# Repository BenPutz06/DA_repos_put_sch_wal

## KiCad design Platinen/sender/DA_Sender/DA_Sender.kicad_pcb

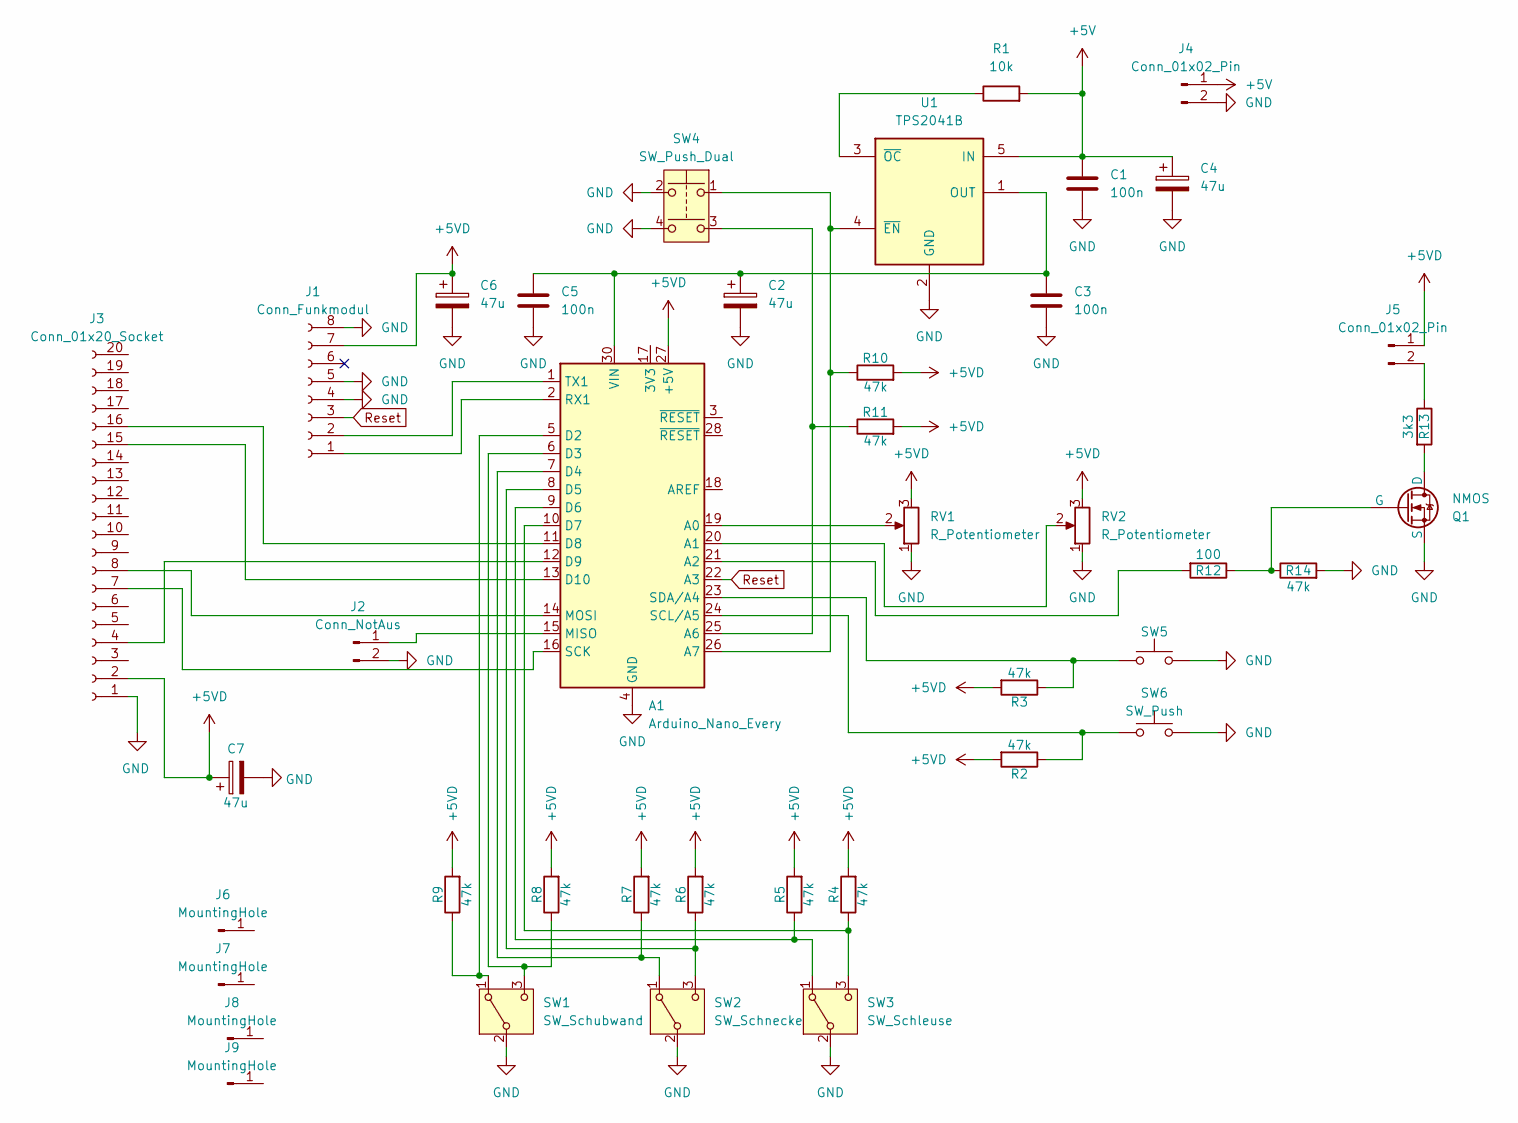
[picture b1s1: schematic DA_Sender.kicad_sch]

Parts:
A1: Arduino_Nano_Every; Arduino_Nano
C1, C3, C5: 100n; C_0805_2012Metric
C2, C4, C6, C7: 47u; CP_EIA-7343-30_AVX-N
J1: Conn_Funkmodul; PinHeader_1x08_P2.54mm_Horizontal
J2: Conn_NotAus; PinHeader_1x02_P2.54mm_Horizontal
J3: Conn_01x20_Socket; PinHeader_1x20_P2.54mm_Vertical
J4: Conn_01x02_Pin; PinHeader_1x02_P2.54mm_Horizontal
J5: Conn_01x02_Pin; PinHeader_1x02_P2.54mm_Vertical
J6, J7, J8, J9: MountingHole; MountingHole_2.7mm_M2.5
Q1: NMOS; TSOT-23; Part-NO FDV305N
R1: 10k; R_0805_2012Metric
R2, R3, R4, R5, R6, R7, R8, R9, R10, R11: 47k; R_0805_2012Metric
R12: 100; R_0805_2012Metric
R13: 3k3; R_0805_2012Metric; Part-NO CRG0603F3K3
R14: 47k; R_0805_2012Metric; Part-NO CRG0603F22K
RV1, RV2: R_Potentiometer; PinHeader_1x03_P2.54mm_Horizontal
SW1: SW_Schubwand; PinHeader_1x03_P2.54mm_Horizontal
SW2: SW_Schnecke; PinHeader_1x03_P2.54mm_Horizontal
SW3: SW_Schleuse; PinHeader_1x03_P2.54mm_Horizontal
SW4: SW_Push_Dual; PinHeader_1x03_P2.54mm_Horizontal
SW5, SW6: SW_Push; PinHeader_1x02_P2.54mm_Horizontal
U1: TPS2041B; SOIC-8_3.9x4.9mm_P1.27mm

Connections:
+5V: C1.1, C4.1, J4.1, R1.2, U1.5 (IN)
+5VD: A1.27 (+5V), C6.1, C7.1, J1.7, J3.2, J5.1, R2.2, R3.2, R4.2, R5.2, R6.2, R7.2, R8.2, R9.2, R10.2, R11.2, RV1.3, RV2.3
GND: A1.4 (GND), A1.29 (GND), C1.2, C2.2, C3.2, C4.2, C5.2, C6.2, C7.2, J1.4, J1.5, J1.8, J2.2, J3.1, J4.2, Q1.2 (S), R14.2, RV1.1, RV2.1, SW1.2 (B), SW2.2 (B), SW3.2 (B), SW4.2, SW4.4, SW5.2, SW6.2, U1.2 (GND)
unnamed: A1.19 (A0), RV1.2
unnamed: A1.20 (A1), RV2.2
unnamed: A1.21 (A2), R12.2
unnamed: A1.25 (A6), R11.1, SW4.3
unnamed: A1.26 (A7), R10.1, SW4.1, U1.4 (~EN)
unnamed: A1.5 (D2), R9.1, SW1.1 (A)
unnamed: A1.6 (D3), R8.1, SW1.3 (C)
unnamed: A1.7 (D4), R7.1, SW2.1 (A)
unnamed: A1.8 (D5), R6.1, SW2.3 (C)
unnamed: A1.9 (D6), R5.1, SW3.1 (A)
unnamed: A1.10 (D7), R4.1, SW3.3 (C)
unnamed: A1.11 (D8), J3.16
unnamed: A1.12 (D9), J3.4
unnamed: A1.13 (D10), J3.15
unnamed: A1.15 (MISO), J2.1
unnamed: A1.14 (MOSI), J3.8
unnamed: A1.2 (RX1), J1.1
unnamed: A1.16 (SCK), J3.7
unnamed: A1.24 (SCL/A5), R2.1, SW6.1
unnamed: A1.23 (SDA/A4), R3.1, SW5.1
unnamed: A1.1 (TX1), J1.2
unnamed: A1.30 (VIN), C2.1, C3.1, C5.1, U1.1 (OUT)
unnamed: J5.2, R13.1
unnamed: Q1.3 (D), R13.2
unnamed: Q1.1 (G), R12.1, R14.1
unnamed: R1.1, U1.3 (~OC)
Reset: A1.22 (A3), J1.3

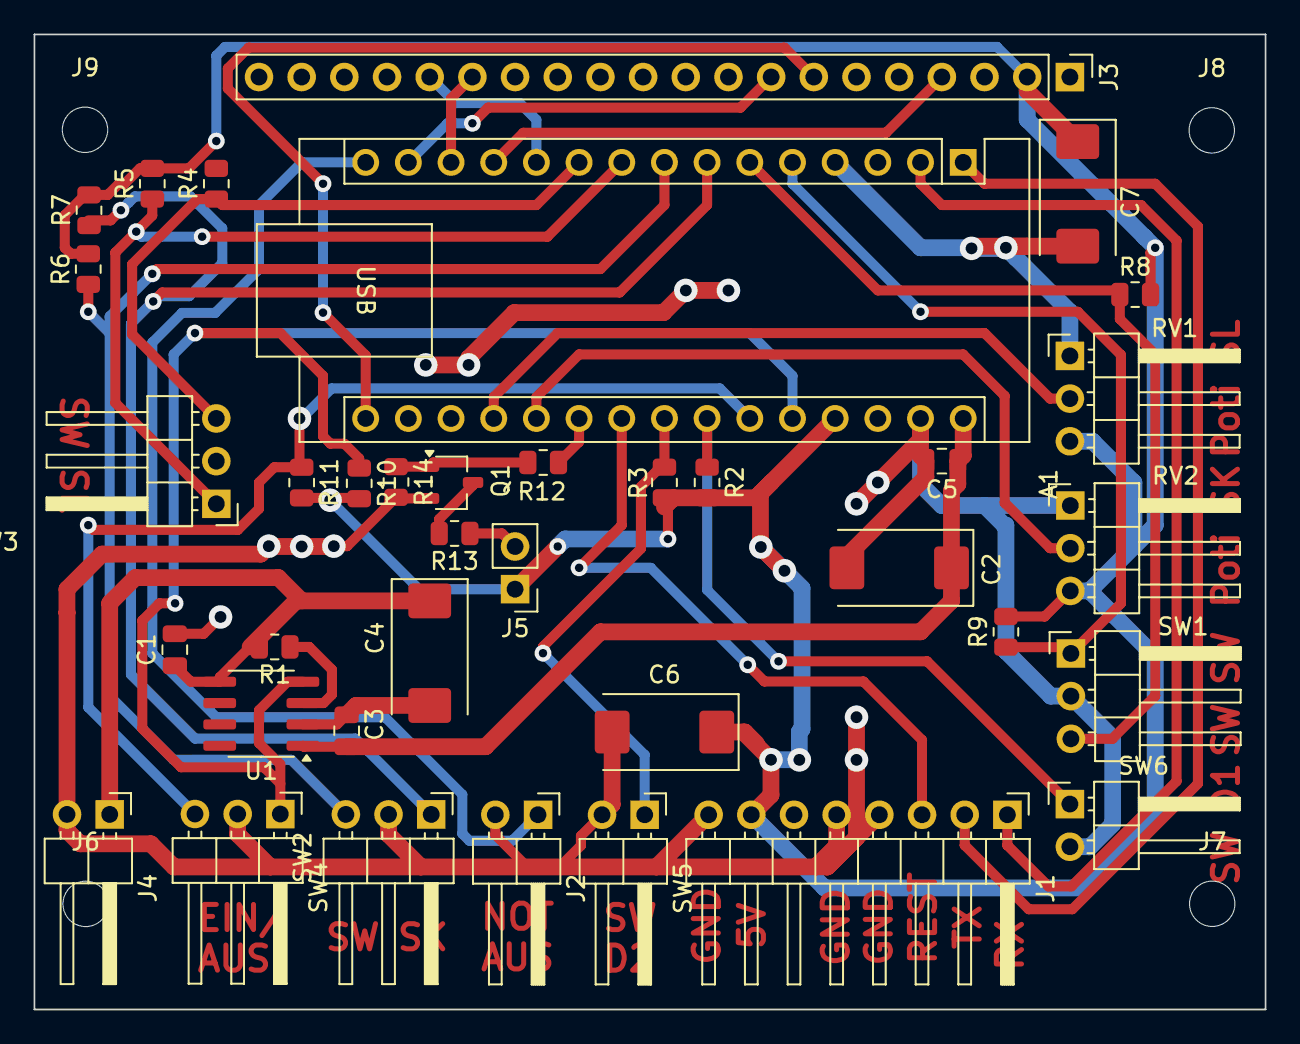
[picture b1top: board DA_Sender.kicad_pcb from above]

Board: 2 copper layers, 73.3 x 58.0 mm, 41 parts (0 on the bottom side), 30 nets.

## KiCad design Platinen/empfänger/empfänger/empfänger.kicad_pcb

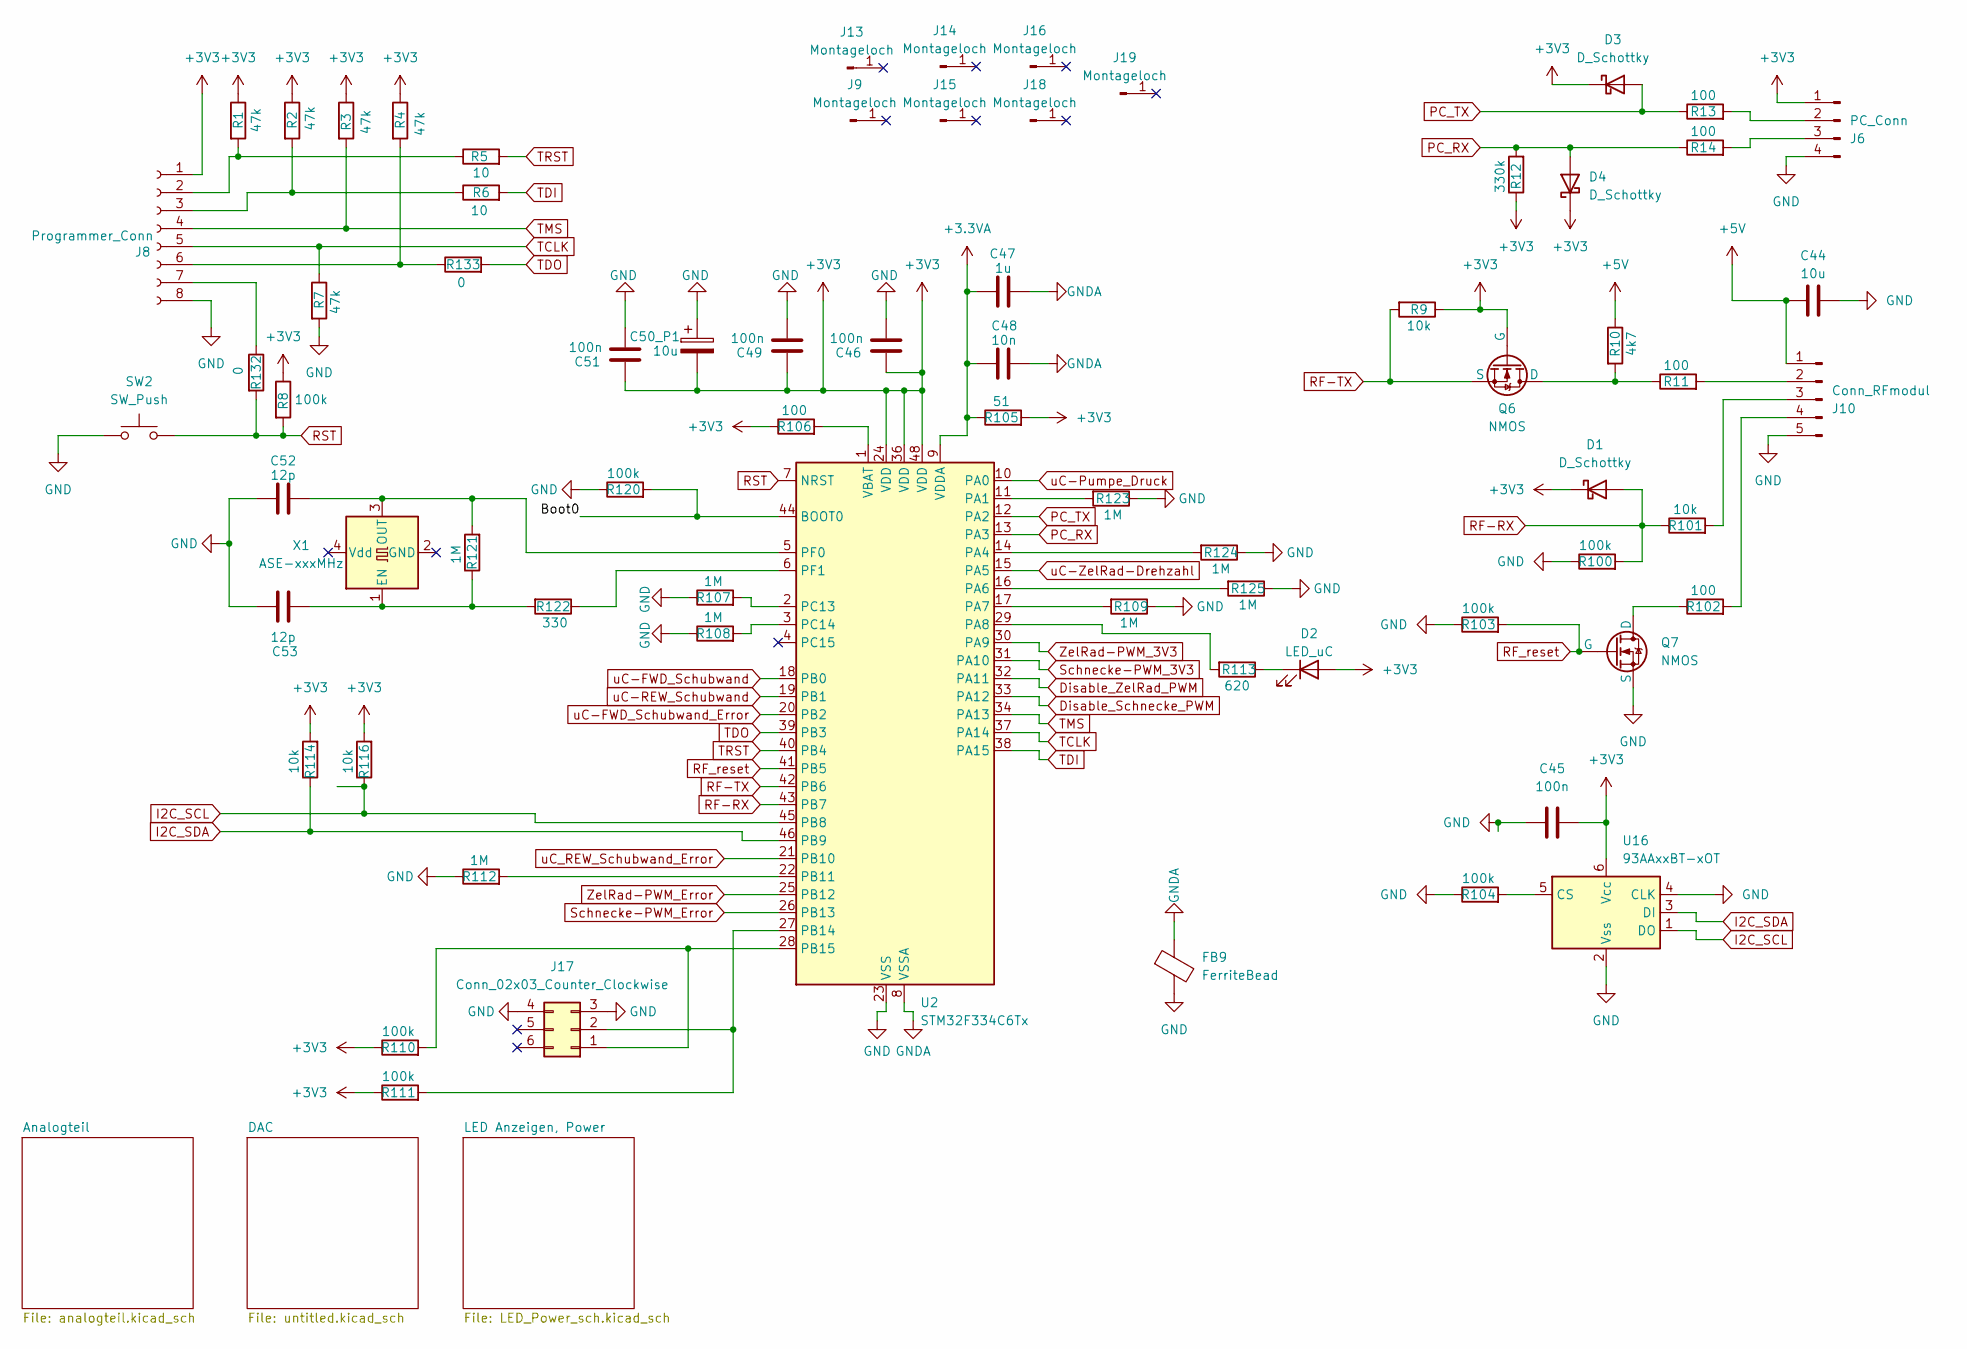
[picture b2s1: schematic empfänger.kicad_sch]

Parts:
C44: 10u; C_1206_3216Metric; Part-NO C1206C106K4RAC
C45, C46, C49, C51: 100n; C_0805_2012Metric; Part-NO CC0805KRX7R9BB104
C47: 1u; C_1206_3216Metric; Part-NO C1206C105K4RAC
C48: 10n; C_0603_1608Metric; Part-NO CC0603KRX7R9BB103
C50_P1: 10u; C_1206_3216Metric; Part-NO B45196H2106K109
C52, C53: 12p; C_0603_1608Metric; Part-NO CC0603JRNPO9BN120
D1, D3, D4: D_Schottky; D_SOD-123; Part-NO MBR0530_30V_0A5
D2: LED_uC; LED_0603_1608Metric; Part-NO SML_512MW
FB9: FerriteBead; R_1206_3216Metric; Part-NO WE-CBF_74279218
J6: PC_Conn; TerminalBlock_Phoenix_PTSM-0,5-4-2.5-V-THR_1x04_P2.50mm_Ver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; Part-NO MCV-0_5-4-G-2_5
J8: Programmer_Conn; Molex_PicoBlade_53047-0810_1x08_P1.25mm_Vertical; Part-NO 53047-0810
J9, J13, J14, J15, J16, J18, J19: Montageloch; MountingHole_5mm
J10: Conn_RFmodul; TeminalBlock_Phoenix_5Pol; Part-NO MCV-0_5-5-G-2_5
J17: Conn_02x03_Counter_Clockwise; PinHeader_2x03_P2.54mm_Vertical; Part-NO TSW-102-07-T-T
Q6, Q7: NMOS; TSOT-23; Part-NO FDV305N
R1, R2, R3, R4, R7: 47k; R_0603_1608Metric; Part-NO CRG0603F47K
R5, R6: 10; R_0603_1608Metric
R8, R100, R103, R104, R110, R111, R120: 100k; R_0603_1608Metric; Part-NO CRG0603F100K
R9, R101, R114, R116: 10k; R_0603_1608Metric; Part-NO CRG0603F10K
R10: 4k7; R_0603_1608Metric; Part-NO CRG0603F4K7
R11, R102, R106: 100; R_0603_1608Metric
R12: 330k; R_0603_1608Metric; Part-NO CRG0603F100R
R13, R14: 100; R_1206_3216Metric
R105: 51; R_1206_3216Metric; Part-NO CRG1206F51R
R107, R108, R109, R112, R121, R123, R124, R125: 1M; R_0603_1608Metric; Part-NO CRG0603F1M0
R113: 620; R_0603_1608Metric; Part-NO CRG0603F620R
R122: 330; R_0603_1608Metric; Part-NO CRG0603F330R
R132, R133: 0; R_0603_1608Metric; Part-NO CRG0603ZR
SW2: SW_Push; SW_Push_1P1T_NO_6x6mm_H9.5mm; Part-NO PHAP3368
U2: STM32F334C6Tx; LQFP-48_7x7mm_P0.5mm; Part-NO STM32F334C6T6TRDKR
U16: 93AAxxBT-xOT; SOT-23-6; Part-NO 24AA025E48
X1: ASE-xxxMHz; Crystal_SMD_5032-4Pin_5.0x3.2mm; Part-NO Q_8_JXG53P4-12-30/50-LF-T1

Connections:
+3.3VA: C47.2, C48.2, R105.1, U2.9 (VDDA); also elsewhere on the board
+3V3: C45.2, C46.2, C49.2, C50_P1.2, C51.2, D1.1 (K), D2.2 (A), D3.1 (K), D4.1 (K), J6.1, J8.1, Q6.1 (G), R1.1, R2.1, R3.1, R4.1, R8.1, R9.1, R12.1, R105.2, R106.1, R110.1, R111.1, R114.2, R116.2, U2.24 (VDD), U2.36 (VDD), U2.48 (VDD), U16.6 (Vcc); also elsewhere on the board
+5V: C44.1, J10.1, R10.1
/Boot0: R120.2, U2.44 (BOOT0)
Disable_Schnecke_PWM: U2.33 (PA12); also elsewhere on the board
Disable_ZelRad_PWM: U2.32 (PA11); also elsewhere on the board
GND: C44.2, C45.1, C46.1, C49.1, C50_P1.1, C51.1, C52.2, C53.1, FB9.2, J6.4, J8.8, J10.5, J17.3, J17.4, Q7.2 (S), R7.2, R100.1, R103.1, R104.1, R107.1, R108.1, R109.1, R112.1, R120.1, R123.1, R124.1, R125.1, SW2.1, U2.23 (VSS), U2.35 (VSS), U2.47 (VSS), U16.2 (Vss), U16.4 (CLK); also elsewhere on the board
GNDA: C47.1, C48.1, FB9.1, U2.8 (VSSA); also elsewhere on the board
I2C_SCL: R116.1, U2.45 (PB8), U16.1 (DO)
I2C_SDA: R114.1, U2.46 (PB9), U16.3 (DI)
unnamed: D2.1 (K), R113.1
unnamed: J6.2, R13.2
unnamed: J6.3, R14.2
unnamed: J8.2, R1.2, R5.1
unnamed: J8.3, R2.2, R6.1
unnamed: J8.6, R4.2, R133.1
unnamed: J8.7, R132.1
unnamed: J10.2, R11.2
unnamed: J10.3, R101.2
unnamed: J10.4, R102.2
unnamed: J17.1, R110.2, U2.28 (PB15)
unnamed: J17.2, R111.2, U2.27 (PB14)
unnamed: Q6.3 (D), R10.2, R11.1
unnamed: Q7.3 (D), R102.1
unnamed: R123.2, U2.11 (PA1)
unnamed: R124.2, U2.14 (PA4)
unnamed: R125.2, U2.16 (PA6)
unnamed: R109.2, U2.17 (PA7)
unnamed: R113.2, U2.29 (PA8)
unnamed: R112.2, U2.22 (PB11)
unnamed: R107.2, U2.2 (PC13)
unnamed: R108.2, U2.3 (PC14)
unnamed: C52.1, R121.2, U2.5 (PF0), X1.3 (OUT)
unnamed: R122.1, U2.6 (PF1)
unnamed: R106.2, U2.1 (VBAT)
unnamed: R104.2, U16.5 (CS)
unnamed: C53.2, R121.1, R122.2, X1.1 (EN)
PC_RX: D4.2 (A), R12.2, R14.1, U2.13 (PA3)
PC_TX: D3.2 (A), R13.1, U2.12 (PA2)
RF-RX: D1.2 (A), R100.2, R101.1, U2.43 (PB7)
RF-TX: Q6.2 (S), R9.2, U2.42 (PB6)
RF_reset: Q7.1 (G), R103.2, U2.41 (PB5)
RST: R8.2, R132.2, SW2.2, U2.7 (NRST)
Schnecke-PWM_3V3: U2.31 (PA10); also elsewhere on the board
Schnecke-PWM_Error: U2.26 (PB13); also elsewhere on the board
TCLK: J8.5, R7.1, U2.37 (PA14)
TDI: R6.2, U2.38 (PA15)
TDO: R133.2, U2.39 (PB3)
TMS: J8.4, R3.2, U2.34 (PA13)
TRST: R5.2, U2.40 (PB4)
ZelRad-PWM_3V3: U2.30 (PA9); also elsewhere on the board
ZelRad-PWM_Error: U2.25 (PB12); also elsewhere on the board
uC-FWD_Schubwand: U2.18 (PB0); also elsewhere on the board
uC-FWD_Schubwand_Error: U2.20 (PB2); also elsewhere on the board
uC-Pumpe_Druck: U2.10 (PA0); also elsewhere on the board
uC-REW_Schubwand: U2.19 (PB1); also elsewhere on the board
uC-ZelRad-Drehzahl: U2.15 (PA5); also elsewhere on the board
uC_REW_Schubwand_Error: U2.21 (PB10); also elsewhere on the board

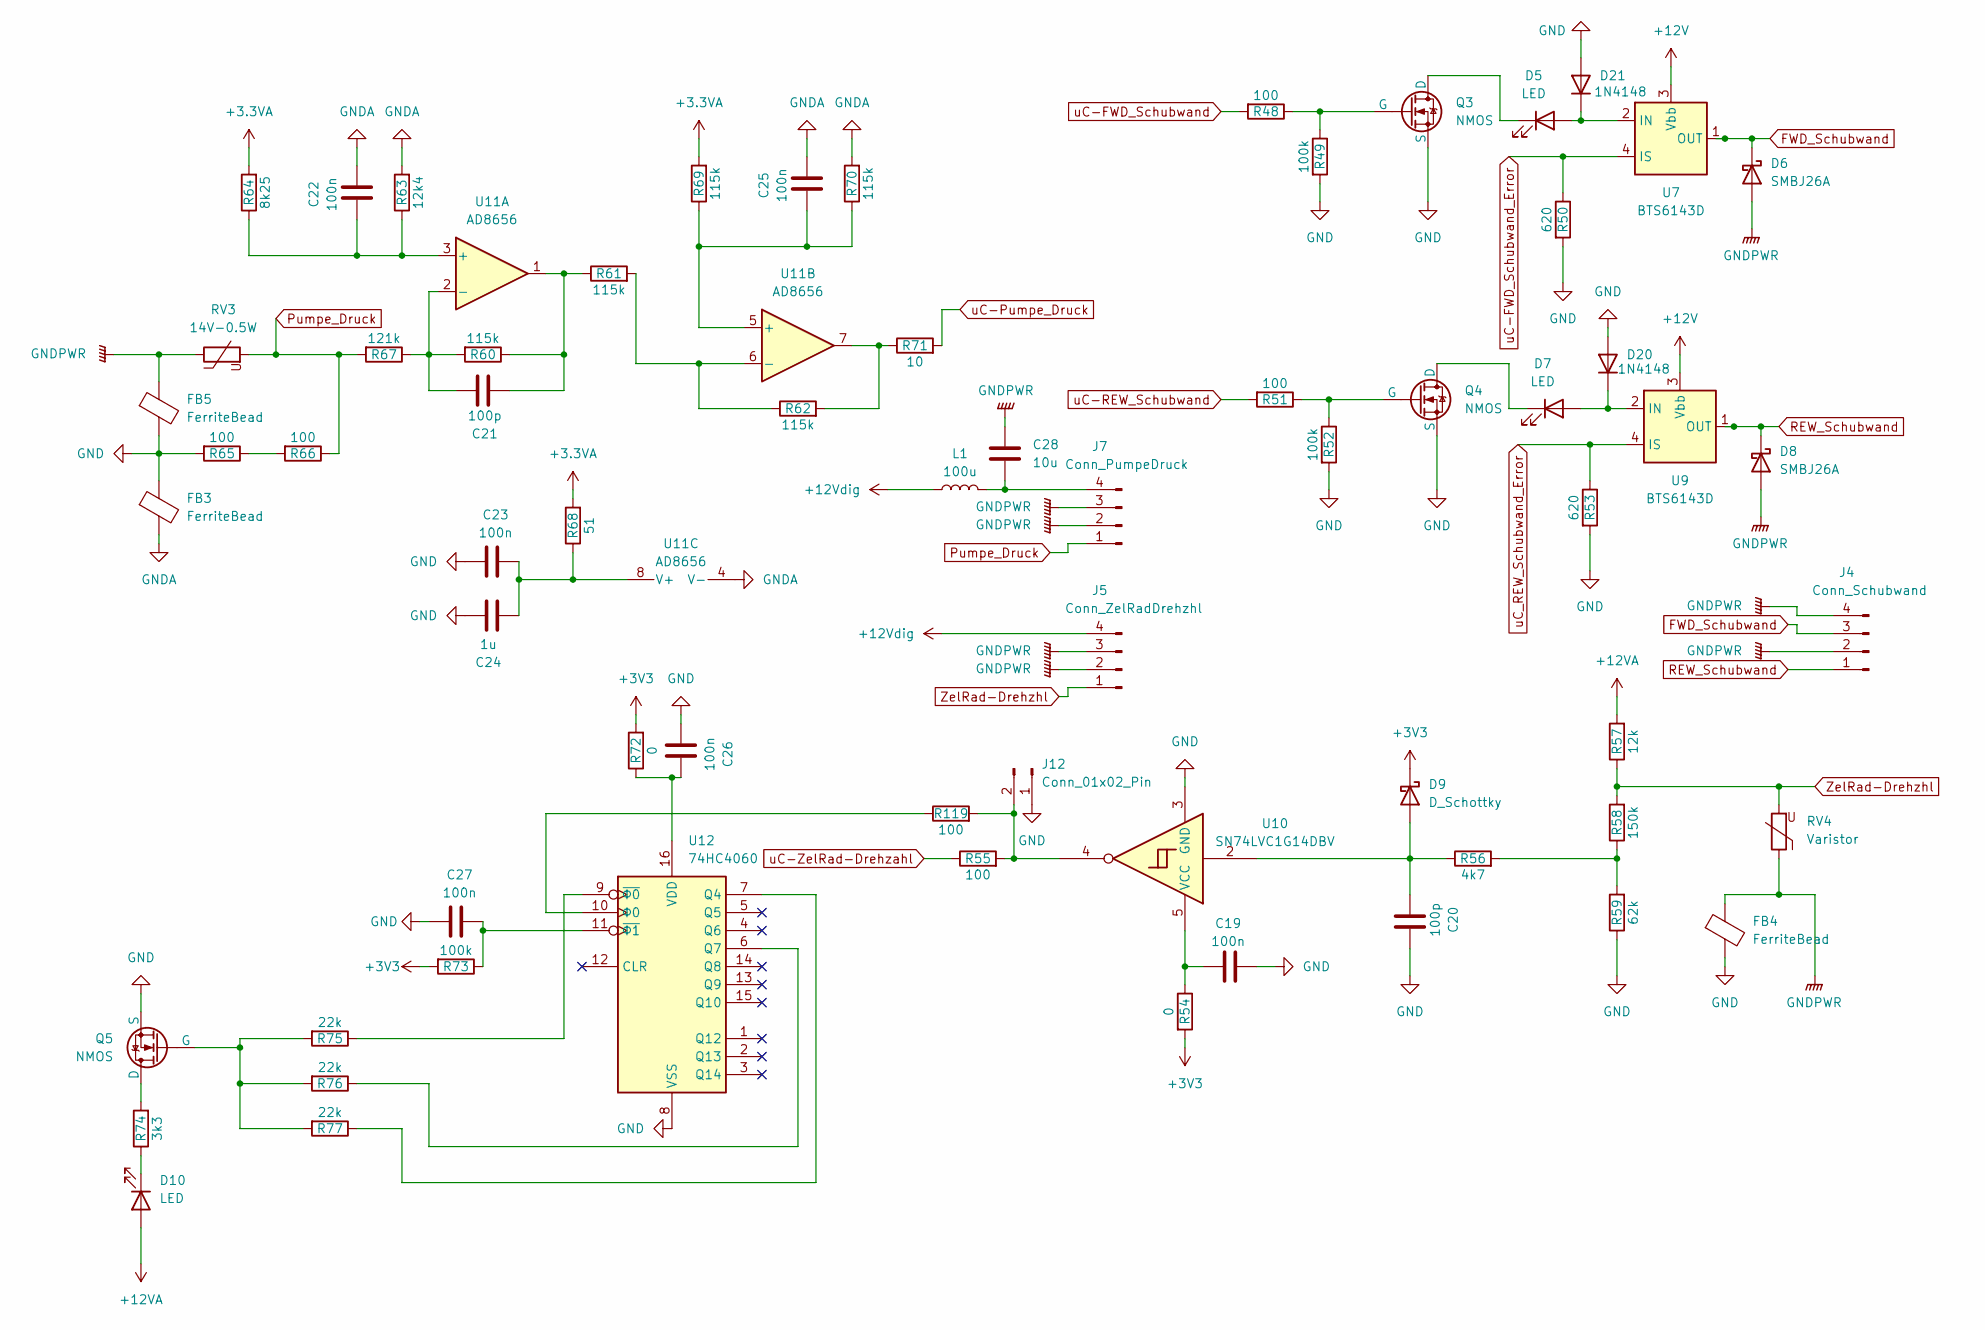
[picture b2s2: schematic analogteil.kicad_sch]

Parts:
C19, C22, C25, C26, C27: 100n; C_0805_2012Metric; Part-NO CC0805KRX7R9BB104
C20, C21: 100p; C_0805_2012Metric; Part-NO C0805C101J5GACTU
C23: 100n; C_0805_2012Metric; Part-NO CC0603KRX7R9BB103
C24: 1u; C_1206_3216Metric; Part-NO C1206C105K4RAC
C28: 10u; C_1206_3216Metric; Part-NO C1206C106K4RAC
D5, D7, D10: LED; LED_0805_2012Metric; Part-NO XZCDGK54W-1VF
D6, D8: SMBJ26A; D_SMB; Part-NO SMBJ26A
D9: D_Schottky; D_SOD-123; Part-NO MBR0530_30V_0A5
D20, D21: 1N4148; D_DO-35_SOD27_P2.54mm_Vertical_AnodeUp; Part-NO 1N4148WS_ES_08
FB3, FB4, FB5: FerriteBead; R_1206_3216Metric; Part-NO WE-CBF_74279218
J4: Conn_Schubwand; PhoenixContact_MSTBVA_2,5_4-G-5,08_1x04_P5.08mm_Vertical; Part-NO MSTBV2_5/4-G-5_08
J5: Conn_ZelRadDrehzhl; PhoenixContact_MSTBVA_2,5_4-G-5,08_1x04_P5.08mm_Vertical; Part-NO MSTBV2_5/4-G-5_08
J7: Conn_PumpeDruck; PhoenixContact_MSTBVA_2,5_4-G-5,08_1x04_P5.08mm_Vertical; Part-NO MSTBV2_5/4-G-5_08
J12: Conn_01x02_Pin; PinHeader_1x02_P2.54mm_Vertical; Part-NO JMP_1X2P_0901200122
L1: 100u; L_Sunlord_SWPA6045S; Part-NO 74404064101
Q3, Q4, Q5: NMOS; TSOT-23; Part-NO FDV305N
R48, R51, R55, R119: 100; R_0603_1608Metric
R49, R52, R73: 100k; R_0603_1608Metric; Part-NO CRG0603F100K
R50, R53: 620; R_0603_1608Metric; Part-NO CRG0603F620R
R54, R72: 0; R_0603_1608Metric; Part-NO CRG0603ZR
R56: 4k7; R_0603_1608Metric; Part-NO CRG0603F4K7
R57: 12k; R_1206_3216Metric; Part-NO CRG1206F12K
R58: 150k; R_0603_1608Metric; Part-NO CRG0603F150K
R59: 62k; R_0603_1608Metric; Part-NO CRG0603F62K
R60, R61, R62, R69, R70: 115k; R_0805_2012Metric; Part-NO RR1220Q-1153-D-M
R63: 12k4; R_0805_2012Metric; Part-NO RR1220Q-1242-D-M
R64: 8k25; R_0805_2012Metric; Part-NO RR1220Q-8251-D-M
R65, R66: 100; R_0805_2012Metric
R67: 121k; R_0805_2012Metric; Part-NO RR1220Q-1213-D-M
R68: 51; R_1206_3216Metric; Part-NO CRG1206F51R
R71: 10; R_0603_1608Metric
R74: 3k3; R_0603_1608Metric; Part-NO CRG0603F3K3
R75, R76, R77: 22k; R_0603_1608Metric; Part-NO CRG0603F22K
RV3: 14V-0.5W; R_1206_3216Metric; Part-NO WE-VS_82541110
RV4: Varistor; R_1206_3216Metric; Part-NO WE-VS_82541110
U7, U9: BTS6143D; TO-252-4; Part-NO BTS6143DAUMA1
U10: SN74LVC1G14DBV; SOT-23-5; Part-NO SN74LVC1G14DBVR
U11: AD8656; SOIC-8_3.9x4.9mm_P1.27mm; Part-NO AD8656ARZ
U12: 74HC4060; SOIC-16_3.9x9.9mm_P1.27mm; Part-NO SN74HC4040D

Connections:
+3.3VA: R64.2, R68.2, R69.2; also elsewhere on the board
+3V3: D9.1 (K), R54.2, R72.2, R73.2; also elsewhere on the board
+12V: U7.3 (Vbb), U9.3 (Vbb); also elsewhere on the board
+12VA: D10.2 (A), R57.2; also elsewhere on the board
+12Vdig: J5.4, L1.1; also elsewhere on the board
FWD_Schubwand: D6.1 (K), J4.3, U7.1 (OUT), U7.5 (OUT)
GND: C19.2, C20.2, C23.1, C24.2, C26.1, C27.1, D20.2 (A), D21.2 (A), FB3.1, FB4.2, FB5.2, J12.1, Q3.2 (S), Q4.2 (S), Q5.2 (S), R49.2, R50.2, R52.2, R53.2, R59.1, R65.2, U10.3 (GND), U12.8 (VSS); also elsewhere on the board
GNDA: C22.2, C25.2, FB3.2, R63.2, R70.2, U11.4 (V-); also elsewhere on the board
GNDPWR: C28.1, D6.2 (A), D8.2 (A), FB4.1, FB5.1, J4.2, J4.4, J5.2, J5.3, J7.2, J7.3, RV3.1, RV4.1; also elsewhere on the board
unnamed: C21.1, R60.1, R61.1, U11.1
unnamed: D5.1 (K), Q3.3 (D)
unnamed: D7.1 (K), Q4.3 (D)
unnamed: C20.1, D9.2 (A), R56.1, U10.2
unnamed: D10.1 (K), R74.1
unnamed: D7.2 (A), D20.1 (K), U9.2 (IN)
unnamed: D5.2 (A), D21.1 (K), U7.2 (IN)
unnamed: C28.2, J7.4, L1.2
unnamed: J12.2, R55.2, R119.2, U10.4
unnamed: Q3.1 (G), R48.1, R49.1
unnamed: Q4.1 (G), R51.1, R52.1
unnamed: Q5.3 (D), R74.2
unnamed: Q5.1 (G), R75.2, R76.2, R77.2
unnamed: R56.2, R58.1, R59.2
unnamed: R62.2, R71.1, U11.7
unnamed: R65.1, R66.2
unnamed: C19.1, R54.1, U10.5 (VCC)
unnamed: C22.1, R63.1, R64.1, U11.3 (+)
unnamed: C21.2, R60.2, R67.1, U11.2 (-)
unnamed: C25.1, R69.1, R70.1, U11.5 (+)
unnamed: R61.2, R62.1, U11.6 (-)
unnamed: C23.2, C24.1, R68.1, U11.8 (V+)
unnamed: R77.1, U12.7 (Q4)
unnamed: R76.1, U12.6 (Q7)
unnamed: C26.2, R72.1, U12.16 (VDD)
unnamed: R75.1, U12.9 (~Φ0)
unnamed: C27.2, R73.1, U12.11 (~Φ1)
unnamed: R119.1, U12.10 (Φ0)
Pumpe_Druck: J7.1, R66.1, R67.2, RV3.2
REW_Schubwand: D8.1 (K), J4.1, U9.1 (OUT), U9.5 (OUT)
ZelRad-Drehzhl: J5.1, R57.1, R58.2, RV4.2
uC-FWD_Schubwand: R48.2; also elsewhere on the board
uC-FWD_Schubwand_Error: R50.1, U7.4 (IS); also elsewhere on the board
uC-Pumpe_Druck: R71.2; also elsewhere on the board
uC-REW_Schubwand: R51.2; also elsewhere on the board
uC-ZelRad-Drehzahl: R55.1; also elsewhere on the board
uC_REW_Schubwand_Error: R53.1, U9.4 (IS); also elsewhere on the board

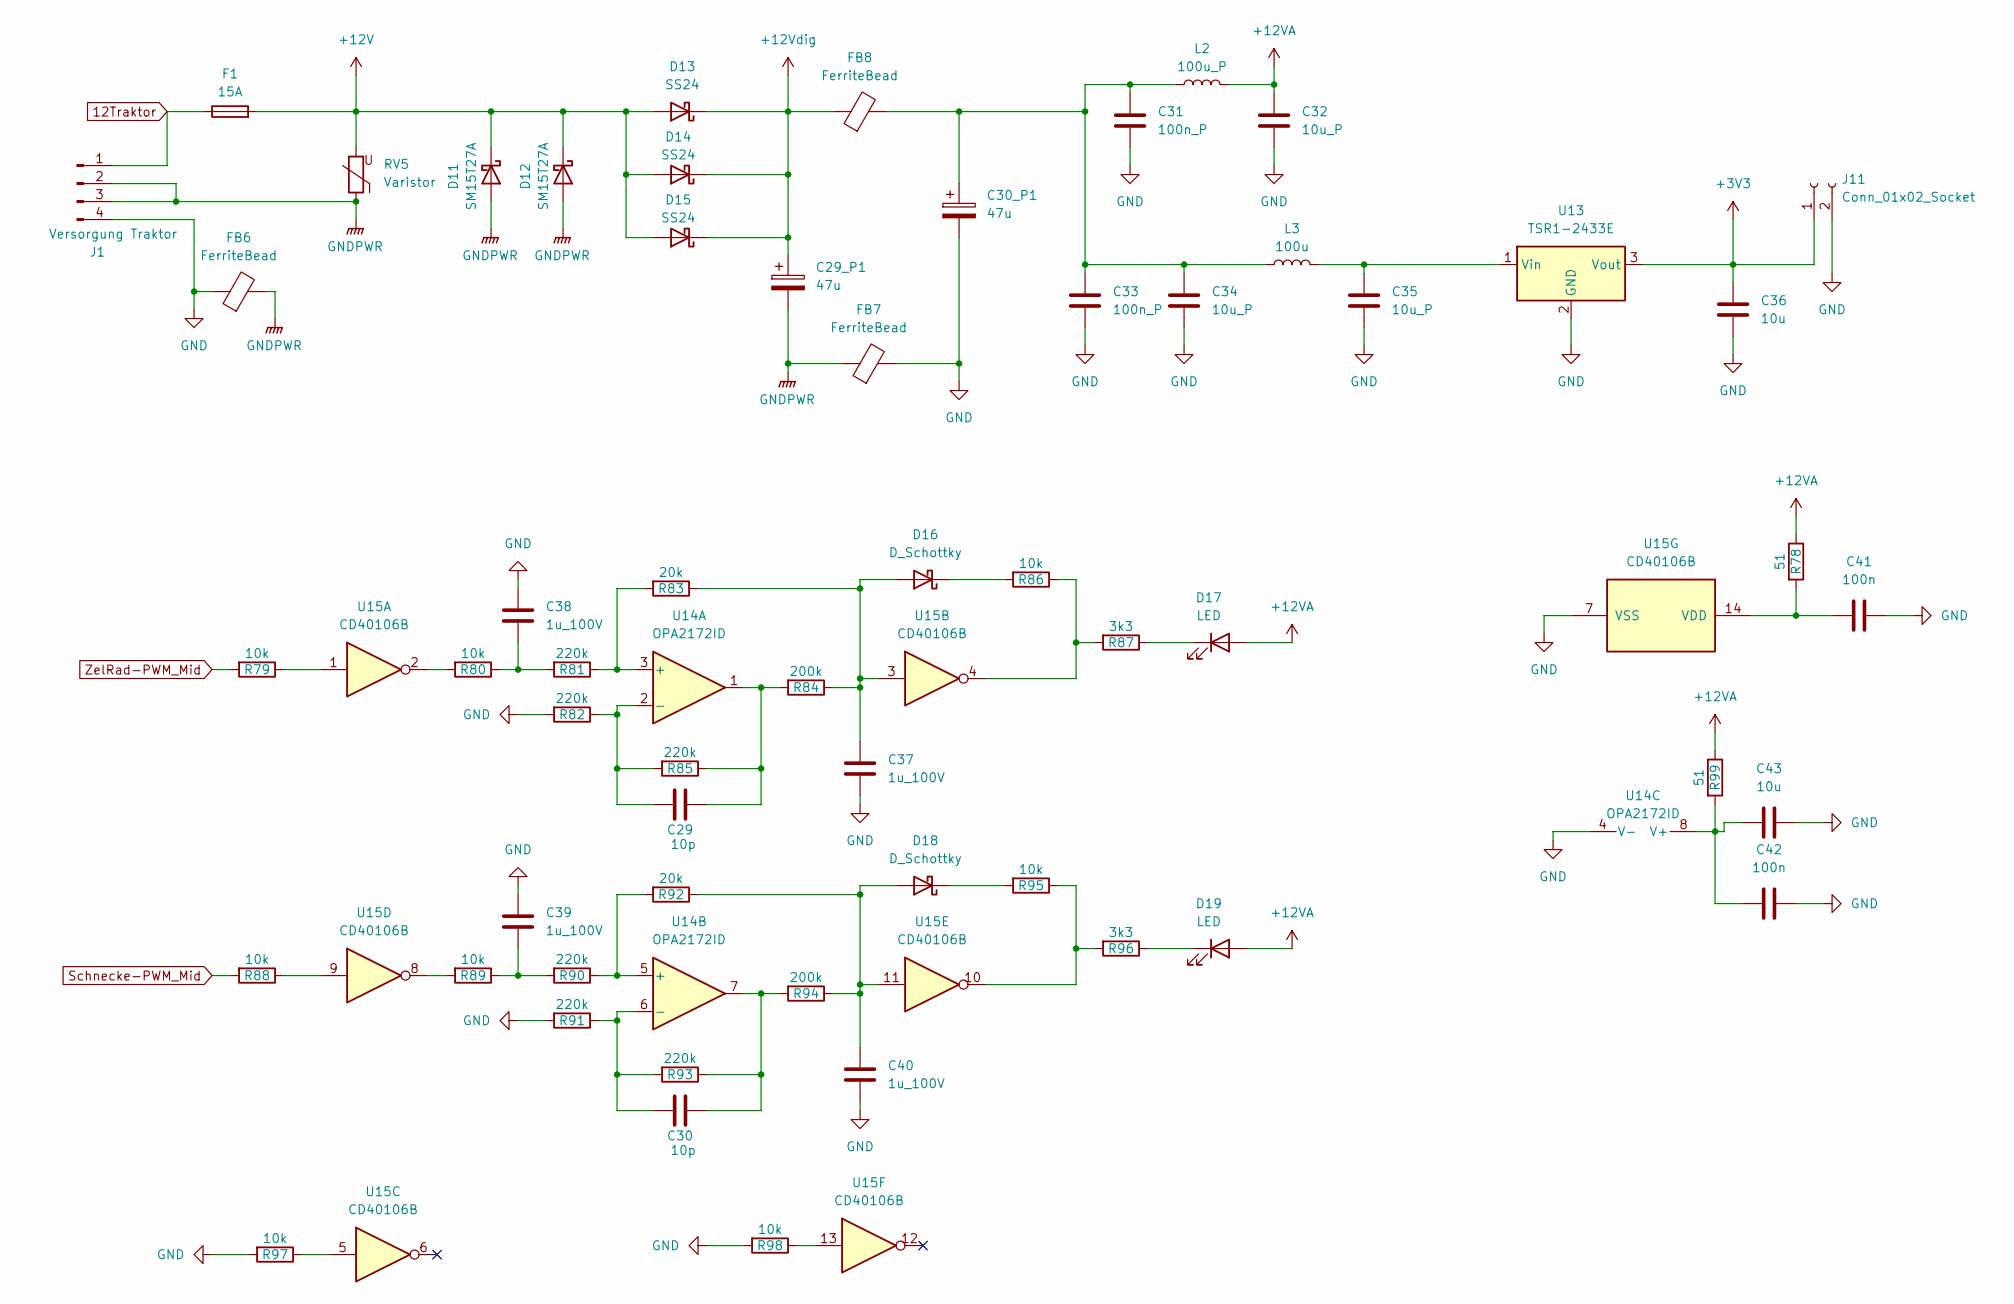
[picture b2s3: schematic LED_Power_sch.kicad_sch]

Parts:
C29, C30: 10p; C_1210_3225Metric; Part-NO 12101C105KAZ2A
C29_P1, C30_P1: 47u; CP_EIA-7343-30_AVX-N; Part-NO TPSE476K025R0080
C31, C33: 100n_P; C_0805_2012Metric; Part-NO CC0805KRX7R9BB104
C32, C34, C35: 10u_P; CP_EIA-3216-18_Kemet-A
C36, C43: 10u; C_1206_3216Metric; Part-NO C1206C106K4RAC
C37, C38, C39, C40: 1u_100V; C_1210_3225Metric; Part-NO 12101C105KAZ2A
C41, C42: 100n; C_0805_2012Metric; Part-NO CC0805KRX7R9BB104
D11, D12: SM15T27A; D_SMC; Part-NO SM15T27A
D13, D14, D15: SS24; D_SMB; Part-NO SS24-M3
D16, D18: D_Schottky; D_SOD-123; Part-NO MBR0530_30V_0A5
D17, D19: LED; LED_0805_2012Metric; Part-NO XZCDGK54W-1VF
F1: 15A; Fuseholder_Blade_Mini_Keystone_3568; Part-NO FUSE-HOLD_01530008Z
FB6, FB7, FB8: FerriteBead; R_1206_3216Metric; Part-NO WE-CBF_74279218
J1: Versorgung Traktor; PhoenixContact_MSTBVA_2,5_4-G-5,08_1x04_P5.08mm_Vertical; Part-NO MSTBV2_5/4-G-5_08
J11: Conn_01x02_Socket; PinHeader_1x02_P2.54mm_Vertical; Part-NO JMP_1X2P_0901200122
L2: 100u_P; L_Sunlord_SWPA6045S
L3: 100u; L_Sunlord_SWPA6045S; Part-NO 74404064101
R78, R99: 51; R_1206_3216Metric; Part-NO CRG1206F51R
R79, R80, R86, R88, R89, R95, R97, R98: 10k; R_0603_1608Metric; Part-NO CRG0603F10K
R81, R82, R85, R90, R91, R93: 220k; R_0603_1608Metric; Part-NO CRG0603F220K
R83, R92: 20k; R_0603_1608Metric; Part-NO CRG0603F20K
R84, R94: 200k; R_0603_1608Metric; Part-NO CRG0603F200K
R87, R96: 3k3; R_0603_1608Metric; Part-NO CRG0603F3K3
RV5: Varistor; Varistor_S20K11-K40; Part-NO B72220S0250K101
U13: TSR1-2433E; TO-220-3_Vertical; Part-NO TSR05-2433
U14: OPA2172ID; SOIC-8_3.9x4.9mm_P1.27mm; Part-NO OPA2172ID
U15: CD40106B; SOIC-14_3.9x8.7mm_P1.27mm; Part-NO CD40106BM96

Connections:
12Traktor: F1.1, J1.1
+3V3: C36.1, J11.1, U13.3 (Vout); also elsewhere on the board
+12V: D11.1 (K), D12.1 (K), D13.2 (A), D14.2 (A), D15.2 (A), F1.2, RV5.2; also elsewhere on the board
+12VA: C32.1, D17.2 (A), D19.2 (A), L2.2, R78.1, R99.1; also elsewhere on the board
+12Vdig: C29_P1.1, D13.1 (K), D14.1 (K), D15.1 (K), FB8.1; also elsewhere on the board
GND: C30_P1.2, C31.2, C32.2, C33.2, C34.2, C35.2, C36.2, C37.1, C38.1, C39.1, C40.1, C41.1, C42.1, C43.1, FB6.1, FB7.2, J1.4, J11.2, R82.2, R91.2, R97.2, R98.2, U13.2 (GND), U14.4 (V-), U15.7 (VSS); also elsewhere on the board
GNDPWR: C29_P1.2, D11.2 (A), D12.2 (A), FB6.2, FB7.1, J1.2, J1.3, RV5.1; also elsewhere on the board
unnamed: C29.2, R84.2, R85.1, U14.1
unnamed: C30.2, R93.1, R94.2, U14.7
unnamed: C30_P1.1, C31.1, C33.1, C34.1, FB8.2, L2.1, L3.1
unnamed: C38.2, R80.1, R81.2
unnamed: C39.2, R89.1, R90.2
unnamed: C37.2, D16.2 (A), R83.1, R84.1, U15.3
unnamed: D16.1 (K), R86.2
unnamed: D17.1 (K), R87.1
unnamed: C40.2, D18.2 (A), R92.1, R94.1, U15.11
unnamed: D18.1 (K), R95.2
unnamed: D19.1 (K), R96.1
unnamed: R79.1, U15.1
unnamed: R80.2, U15.2
unnamed: R86.1, R87.2, U15.4
unnamed: R88.1, U15.9
unnamed: R89.2, U15.8
unnamed: R95.1, R96.2, U15.10
unnamed: R97.1, U15.5
unnamed: R98.1, U15.13
unnamed: C35.1, L3.2, U13.1 (Vin)
unnamed: R81.1, R83.2, U14.3 (+)
unnamed: C29.1, R82.1, R85.2, U14.2 (-)
unnamed: R90.1, R92.2, U14.5 (+)
unnamed: C30.1, R91.1, R93.2, U14.6 (-)
unnamed: C42.2, C43.2, R99.2, U14.8 (V+)
unnamed: C41.2, R78.2, U15.14 (VDD)
Schnecke-PWM_Mid: R88.2; also elsewhere on the board
ZelRad-PWM_Mid: R79.2; also elsewhere on the board

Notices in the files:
empfänger/Pump/Inc/Parameter.h:
(C) COPYRIGHT Benjamin Putz
